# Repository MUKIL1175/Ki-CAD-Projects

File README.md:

# PCB Designs Repository

Welcome to my **PCB Designs Repository**! This repository contains a collection of various **PCB (Printed Circuit Board)** designs created using **KiCad**, a powerful and open-source **EDA (Electronic Design Automation)** tool. The designs span a wide range of applications and are available for download or reference. Feel free to explore, download, and contribute!

## Repository Overview

This repository hosts **PCB designs** suitable for a variety of electronic projects. Each design is organized into individual folders, which contain detailed files and documentation. These designs are open-source and can be used for educational, personal, and professional purposes.

## Key Features

- **KiCad Project Files**: Complete project files for each PCB design.
- **Schematic Diagrams**: Clear and easy-to-understand circuit schematics.
- **Gerber Files**: Ready-to-manufacture Gerber files for PCB fabrication.

## How to Use the Designs

1. **Download the Project Files**:
   Navigate to the specific project folder and download the KiCad project files.

2. **Open in KiCad**:
   Use **KiCad** to open the `.pro` project file. This will provide access to the full project, including the schematic and PCB layout.

3. **Generate Gerber Files**:
   You can generate Gerber files from the KiCad project using the "Plot" option in KiCad, which will be suitable for PCB manufacturing.

4. **Modify and Customize**:
   Feel free to modify the designs as per your project requirements. Always verify that the component specifications and footprints are compatible with your needs.

## Contact for PCB Orders

For professional **PCB orders**, **custom designs**, or any inquiries related to the PCB manufacturing process, please get in touch:

- **Name**: MONAMUKIL SS
- **Email**: [mukil11ss@gmail.com](mailto:mukil11ss@gmail.com)

### Services Offered

I offer a range of services, including:

- Custom PCB designs based on your specifications
- PCB prototyping and manufacturing
- PCB assembly and testing services

## License

All designs in this repository are provided under an **open-source license**. Please check individual design folders for specific license details, if applicable. You are free to use, modify, and distribute the designs under the terms of the respective license.

---

Thank you for visiting my repository! If you find any of the designs useful or have suggestions for improvements, feel free to open an issue or submit a pull request. 

Happy designing!

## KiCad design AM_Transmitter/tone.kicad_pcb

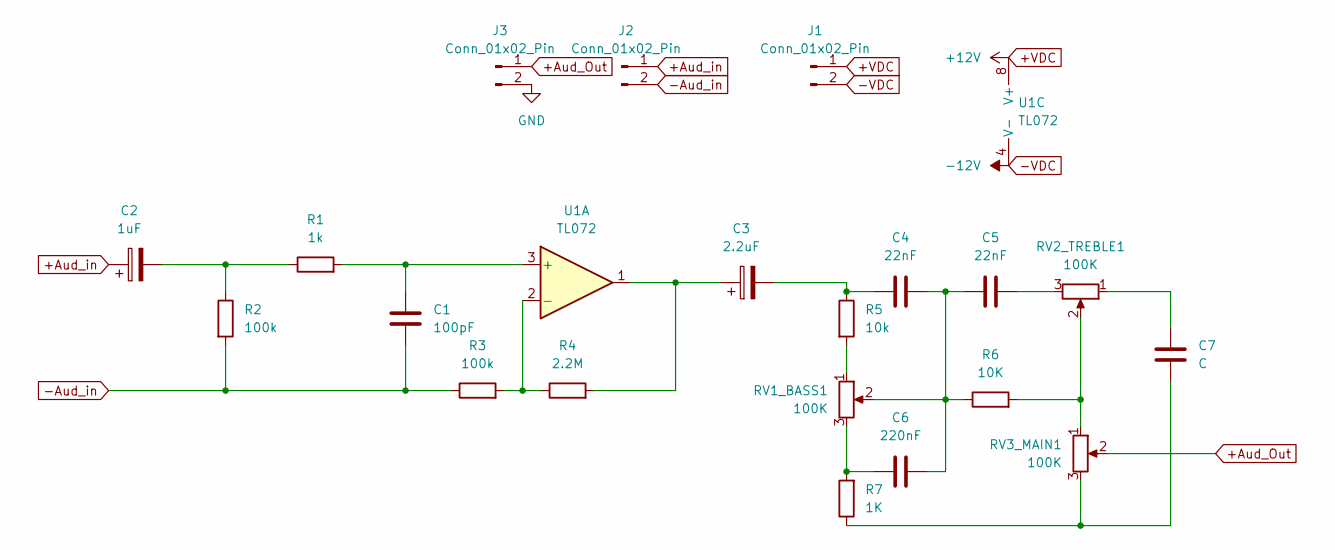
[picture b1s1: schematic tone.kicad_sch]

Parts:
C1: 100pF; C_Disc_D4.7mm_W2.5mm_P5.00mm
C2: 1uF; CP_Radial_D8.0mm_P2.50mm
C3: 2.2uF; CP_Radial_D8.0mm_P2.50mm
C4, C5: 22nF; C_Disc_D4.7mm_W2.5mm_P5.00mm
C6: 220nF; C_Disc_D4.7mm_W2.5mm_P5.00mm
C7: C; C_Disc_D4.7mm_W2.5mm_P5.00mm
J1, J2, J3: Conn_01x02_Pin; PinHeader_1x02_P2.54mm_Vertical
R1: 1k; R_Box_L8.4mm_W2.5mm_P5.08mm
R2, R3: 100k; R_Box_L8.4mm_W2.5mm_P5.08mm
R4: 2.2M; R_Box_L8.4mm_W2.5mm_P5.08mm
R5: 10k; R_Box_L8.4mm_W2.5mm_P5.08mm
R6: 10K; R_Box_L8.4mm_W2.5mm_P5.08mm
R7: 1K; R_Box_L8.4mm_W2.5mm_P5.08mm
RV1_BASS1, RV2_TREBLE1, RV3_MAIN1: 100K; Potentiometer_Alps_RK163_Single_Horizontal
U1: TL072; DIP-8_W7.62mm

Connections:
+Aud_Out: J3.1, RV3_MAIN1.2
+Aud_in: C2.1, J2.1
+VDC: J1.1, U1.8 (V+)
-Aud_in: C1.2, J2.2, R2.2, R3.1
-VDC: J1.2, U1.4 (V-)
GND: J3.2
unnamed: C2.2, R1.1, R2.1
unnamed: C3.1, R4.2, U1.1
unnamed: C3.2, C4.1, R5.1
unnamed: C4.2, C5.1, C6.2, R6.1, RV1_BASS1.2
unnamed: C5.2, RV2_TREBLE1.3
unnamed: C6.1, R7.2, RV1_BASS1.3
unnamed: C7.1, RV2_TREBLE1.1
unnamed: C7.2, R7.1, RV3_MAIN1.3
unnamed: R5.2, RV1_BASS1.1
unnamed: R6.2, RV2_TREBLE1.2, RV3_MAIN1.1
unnamed: C1.1, R1.2, U1.3 (+)
unnamed: R3.2, R4.1, U1.2 (-)

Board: 2 copper layers, 21 parts (0 on the bottom side), 17 nets, no tracks yet.

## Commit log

2024-07-29 intro.txt
2025-01-20 Create txt
2025-01-20 Create about
